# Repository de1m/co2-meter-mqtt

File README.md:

# CO2 Meter (mqtt)

## Description

In this project I've created a co2 sesor (mh-z19) with connection to a mqtt broker, so you cann send the co2 data to a mqtt broker. 

I've used the esp8266 12e version. 

Folder structure:
firmware - all files, that you do need to flash your esp8266 12e
pcb - board schema, pdfs. Imprtant: for the board you need a usb-connection board (show image board_top.jpg)
3d-models - 3d models for 3d printer, so you can print a case for pcb.

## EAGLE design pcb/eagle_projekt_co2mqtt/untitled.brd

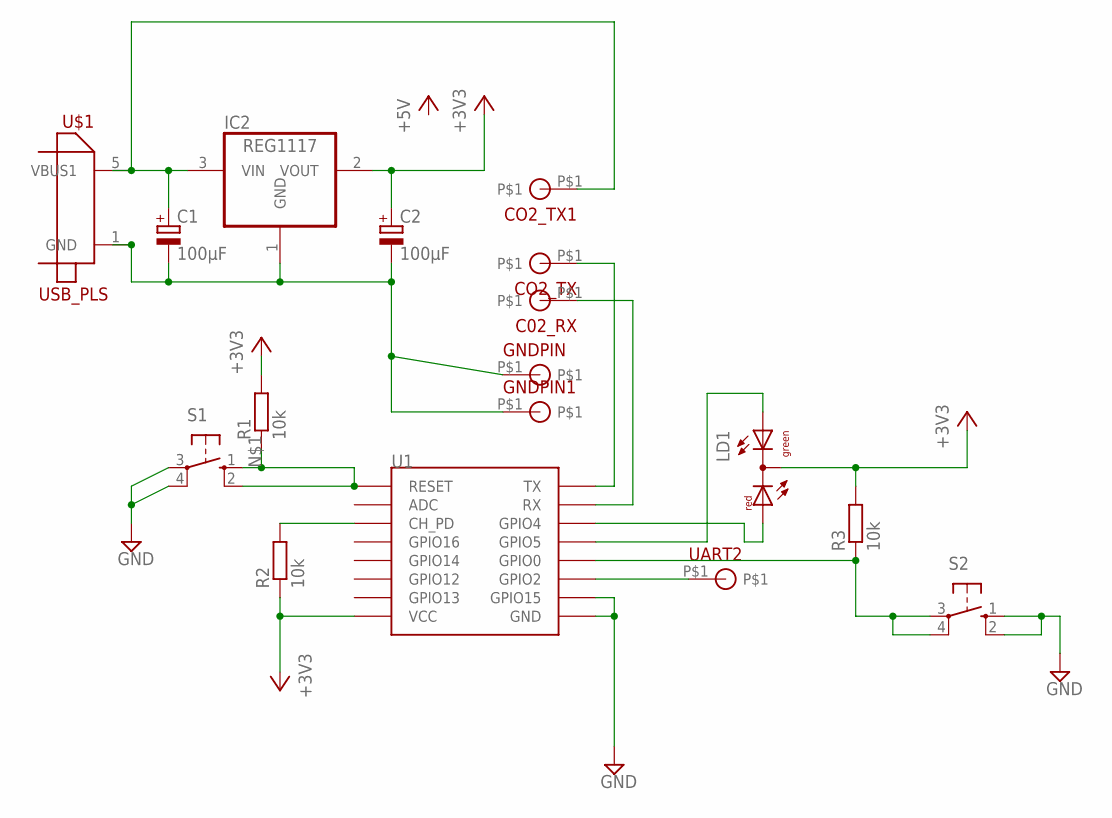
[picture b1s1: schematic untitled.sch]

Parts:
C1, C2: 100µF; E5-6
C02_RX: 1PIN
CO2_TX, CO2_TX1: 1PIN
GNDPIN, GNDPIN1: 1PIN
IC2: REG1117; SOT223
LD1: DUOLED-RG-C; DUOLED-C-5MM
R1, R2, R3: 10k; R0603
S1, S2: 10-XX; B3F-10XX
U1: ESP12
U$1: USB_PLS; USB_PLB
UART2: 1PIN

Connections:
+3V3: C2.+, IC2.2 (VOUT), LD1.C, R1.2, R2.1, R3.2, U1.VCC
+5V: C1.+, CO2_TX1.P$1, IC2.3 (VIN), U$1.5 (VBUS1)
GND: C1.-, C2.-, GNDPIN.P$1, GNDPIN1.P$1, IC2.1 (GND), S1.3, S1.4 (P1), S2.1 (S), S2.2 (S1), U1.GND, U1.GPIO15, U$1.1 (GND)
unnamed: R1.1, S1.1 (S), S1.2 (S1), U1.RESET
unnamed: R3.1, S2.3, S2.4 (P1), U1.GPIO0
unnamed: R2.2, U1.CH_PD
unnamed: LD1.AX (AG), U1.GPIO5
unnamed: LD1.AR, U1.GPIO4
unnamed: U1.GPIO2, UART2.P$1
RX: C02_RX.P$1, U1.RX
TX: CO2_TX.P$1, U1.TX

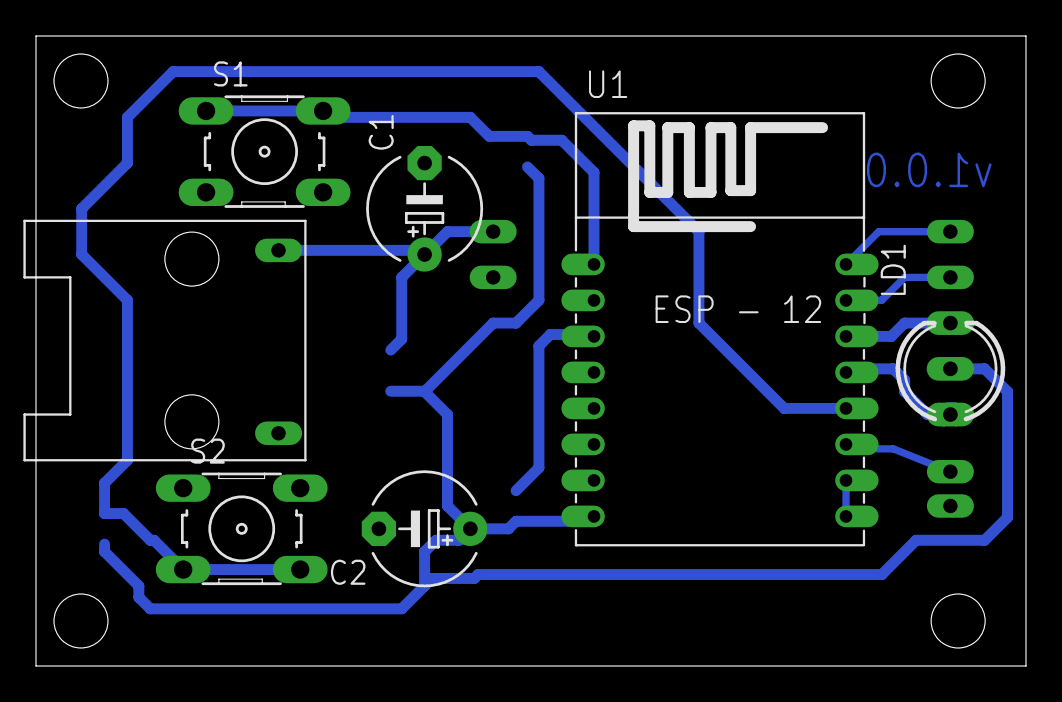
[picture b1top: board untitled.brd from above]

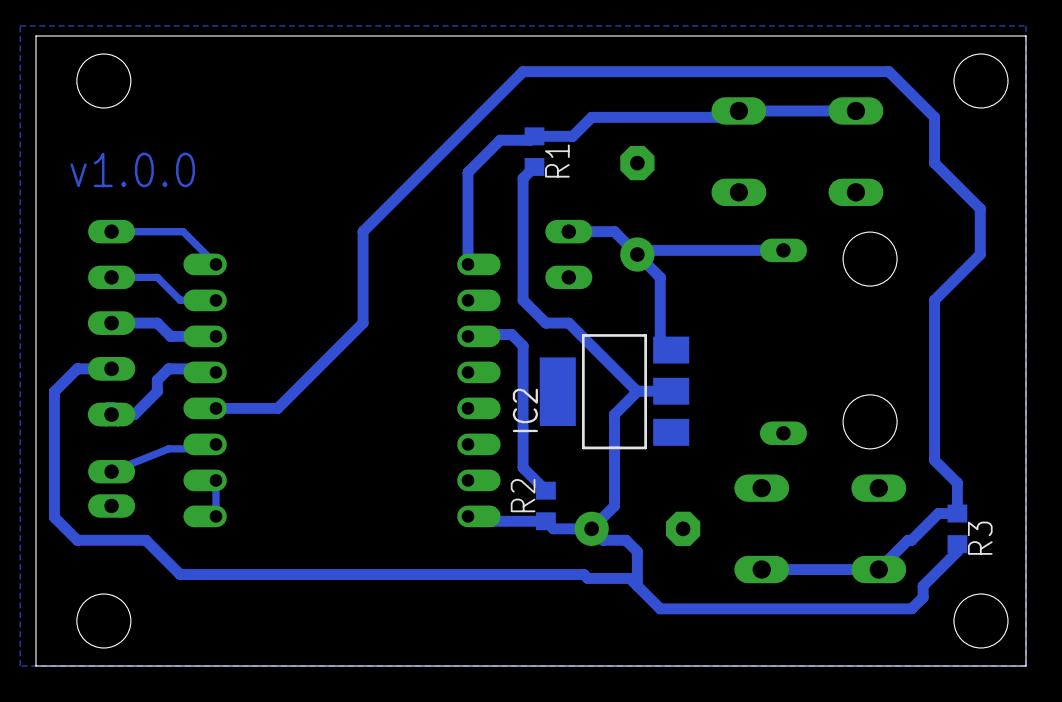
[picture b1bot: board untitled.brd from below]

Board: 2 copper layers, 55.0 x 35.0 mm, 17 parts (4 on the bottom side), 11 nets.

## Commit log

2016-12-04 fix error with htmlform length
2016-12-05 add input check1
2016-12-06 value check continue
2016-12-07 check input continue
2016-12-08 add time couter to reset button, fix erros with write/read flash
2016-12-18 add check mqtt and wifi connection
2016-12-18 add comments, fix error
2017-01-04 remove 7seg display functions
2017-03-26 add pcb, 3d models, readme
2017-03-26 updated image path
